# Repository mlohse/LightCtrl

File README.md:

# LightCtrl

Light Controller for Egret TenV4 electric scooter

The goal of this project is to power the scooter's front light from the main LiPo battery instead of using 4x throw-away alkaline batteries (AAA).
Further, it allows the light to be switched on/off conveniently via the throttle controller's power button (same as the rear light)
or have the light switched on/off automatically when it's getting dark (e.g. in tunnels or at night).

The PCB needs to be installed into the front light's battery compartment. The on/off switch is no longer needed and can be replaced by a photo transistor.

A short demo video (German) is available on vimeo: https://vimeo.com/364582430

# Required Skills
Before you consider building your own, please be aware that you'll need some skills here:

* You should be able to solder SMD! I've chosen large components (1206) for the PCB, but of course there is the 44-pin package of the ATMEGA, which may need some practice and a decent solder iron/station.

* The PCB and front light is powered via the 5V USB supply of the scooters throttle controller and needs to be connected in series to the throttle controller's tx data line (white cable).
  This can be accomplished by either opening/modifying the throttle controller (see instructions below) or creating an adapter cable which can be installed between the throttle and the motor controller (in the battery compartment).

* The front light's plastic case needs some mechanical modification to fit a cable through the housing (drill a hole) and fit PCB into the battery compartment.

* You'll need to remove the front light's on/off switch and solder wire between the voltage regulators enable pin (again SMD) and ground, see description below...

* You'll need an ISP-programmer for flashing the firmware (those are available on Ebay for ~15 Euro)

This project is certainly not suitable for beginners and of course I won't take any liability if you break your scooter or any components of it.

# Bill of Material (BOM)
The PCB can be ordered at OSH Park (they ship worldwide):

* https://oshpark.com/shared_projects/gwnaN0r6 (rev.B)

It doesn't really matter of which brand/type you order resistors and capacitors, nor does this board require any tight tolerances. You can purchase whatever your local hardware dealer has on stock fitting the value/package described by the schematic.
However, for convenience I've created a virtual shopping basket at Reichelt Elektronik:

* https://www.reichelt.de/my/1627216

Unfortunately, the AQY212EH isn't available at Reichelt, but you can order it from Buerklin,
Order-No.: 29G8736

* https://www.buerklin.com/de/Produkte/Elektromechanik/Relais-und-Sch%C3%BCtze/PhotoMOS-Relais/AQY-212-EHA%2C-SMD-Relais/p/29G8736

Further, I've tried several (low-cost) usb cables from Amazon which didn't quite fit my needs, until I came across these 2:

* https://www.amazon.de/gp/product/B01I1HXRK8/ (this is actually much shorter than 40cm, I measured only 34cm!)

* https://www.amazon.de/gp/product/B00P0ES0VC/

The UGreen USB3 extension cable is of decent quality and can be crimped perfectly into the Micromatch connector.
(Yes, it needs to be cut into halves: The female connector is needed for the front light, the male can be used to build an adapter for the ISP programmer)

# Building and Flashing the Firmware
You need to have an AVR toolchain installed (make, gcc, binutils)

On Arch Linux simply install the following packages:

`# pacman -S community/avr-gcc community/avr-binutils community/avr-libc`

I'm still using my good old AVR Dragon (unfortunately, it seems to be out of production), which needs to have avrdude installed:

`# pacman -S avrdude`

If you own a different programmer there is a good chance it's also supported by avrdude, otherwise just install whatever software it needs and don't forget to adopt the programmer/fuses section of the Makefile accordingly.

To build the firmware change into the `src` directory and run:

`# make`

...then connect the board to your ISP programmer (it needs to be powered through the programmer!) and flash the fuses:

`# make fuses`

...and firmware:

`# make program`

Done.

# Front Light PCB Modification
1. Remove the on/off switch and undervoltage indicator led (no longer needed)
2. Connect the voltage regulator's enable pin (outer pin) to GND, as shown:

# Throttle Controller Modification
1. Open the throttle controller (it is glued with silicone and requieres some force - use a knife or sharp piece of metal). Once open remove the USB socket which is also glued in with silicone and clean it as best as you can:

2. Unsolder the TX data wire (white, labels as T6):

3. Open the solder bridge between the USB data lines:

4. Conntect the white cabel (which was soldered to throttle T6 previously) to the USB data line and add a new cable from the other usb data line to the throttle's T6 pin. Note: the 4k7 resistor is optional. If it is installed the scooter can be started without the LightCtrl pcb connected. If it is not fitted, the throttle will show an error if powered on without it. This may be usefull as a weak theft-protection (if you take the front-light with you when you leave the scooter alone).

5. Use some hot glue to put the USB socket back in
Important: After modification the USB socket can no longer be used to charge usb devices! Do not plug in your cell phone!

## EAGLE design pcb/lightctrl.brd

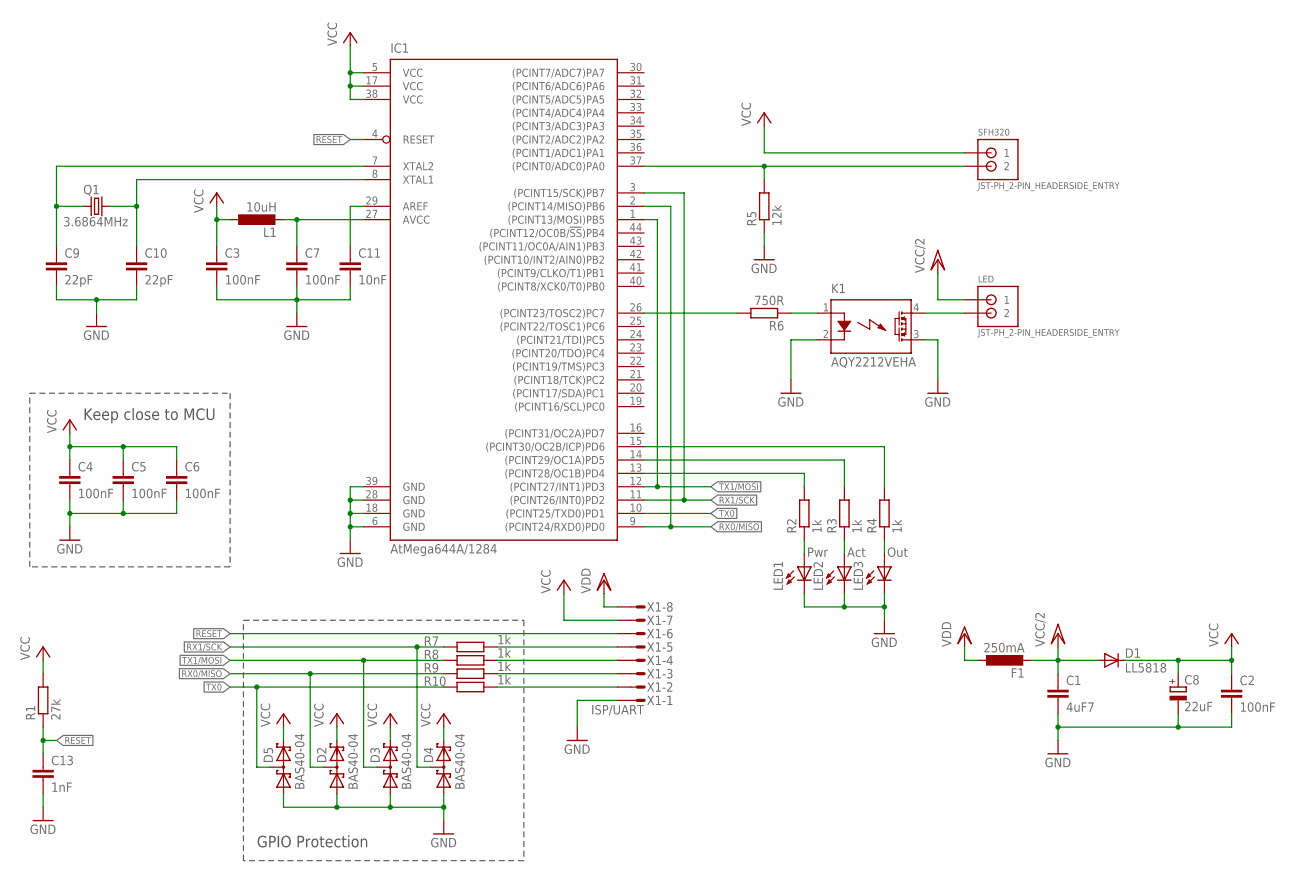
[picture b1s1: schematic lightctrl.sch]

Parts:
C1: 4uF7; C1206
C2, C3, C4, C5, C6, C7: 100nF; C1206
C8: 22uF; SMC_D
C9, C10: 22pF; C1206
C11: 10nF; C1206
C13: 1nF; C1206
D1: LL5818; MELF-MLL41
D2, D3, D4, D5: BAS40-04; SOT23
F1: 250mA; L1812
IC1: AtMega644A/1284; TQFP44
K1: AQY2212VEHA; SMD-DIP04
L1: 10uH; L3230M
LED: JST-PH_2-PIN_HEADERSIDE_ENTRY; S2B-PH_HEADER
LED1: Pwr; CHIPLED_1206
LED2: Act; CHIPLED_1206
LED3: Out; CHIPLED_1206
Q1: 3.6864MHz; HC49UP
R1: 27k; R1206
R2, R3, R4, R7, R8, R9, R10: 1k; R1206
R5: 12k; R1206
R6: 750R; R1206
SFH320: JST-PH_2-PIN_HEADERSIDE_ENTRY; S2B-PH_HEADER
X1: ISP/UART; MICROMATCH-8

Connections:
GND: C1.2, C2.2, C3.2, C4.2, C5.2, C6.2, C7.2, C8.-, C9.2, C10.2, C11.2, C13.2, D2.1 (A1), D3.1 (A1), D4.1 (A1), D5.1 (A1), IC1.6 (GND), IC1.18 (GND), IC1.28 (GND), IC1.39 (GND), K1.2 (K), K1.3 (DS2), LED1.C, LED2.C, LED3.C, R5.1, X1.1
unnamed: C7.1, IC1.27 (AVCC), L1.2
unnamed: IC1.37 ((PCINT0/ADC0)PA0), R5.2, SFH320.P2 (2)
unnamed: C11.1, IC1.29 (AREF)
unnamed: C10.1, IC1.8 (XTAL1), Q1.2
unnamed: C9.1, IC1.7 (XTAL2), Q1.1
unnamed: K1.4 (DS1), LED.P2 (2)
unnamed: LED1.A, R2.1
unnamed: LED2.A, R3.1
unnamed: LED3.A, R4.1
unnamed: IC1.13 ((PCINT28/OC1B)PD4), R2.2
unnamed: IC1.14 ((PCINT29/OC1A)PD5), R3.2
unnamed: IC1.15 ((PCINT30/OC2B/ICP)PD6), R4.2
unnamed: R7.2, X1.5
unnamed: K1.1 (A), R6.1
unnamed: R8.2, X1.4
unnamed: R9.2, X1.3
unnamed: IC1.26 ((PCINT23/TOSC2)PC7), R6.2
unnamed: R10.2, X1.2
RESET: C13.1, IC1.4 (RESET), R1.1, X1.6
RX0/MISO: D2.3 (C1A2), IC1.2 ((PCINT14/MISO)PB6), IC1.9 ((PCINT24/RXD0)PD0), R9.1
RX1/SCK: D4.3 (C1A2), IC1.3 ((PCINT15/SCK)PB7), IC1.11 ((PCINT26/INT0)PD2), R7.1
TX0: D5.3 (C1A2), IC1.10 ((PCINT25/TXD0)PD1), R10.1
TX1/MOSI: D3.3 (C1A2), IC1.1 ((PCINT13/MOSI)PB5), IC1.12 ((PCINT27/INT1)PD3), R8.1
VCC: C2.1, C3.1, C4.1, C5.1, C6.1, C8.+, D1.C, D2.2 (C2), D3.2 (C2), D4.2 (C2), D5.2 (C2), IC1.5 (VCC), IC1.17 (VCC), IC1.38 (VCC), L1.1, R1.2, SFH320.P1 (1), X1.7
VCC/2: C1.1, D1.A, F1.2, LED.P1 (1)
VDD: F1.1, X1.8

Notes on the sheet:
GPIO Protection
Keep close to MCU

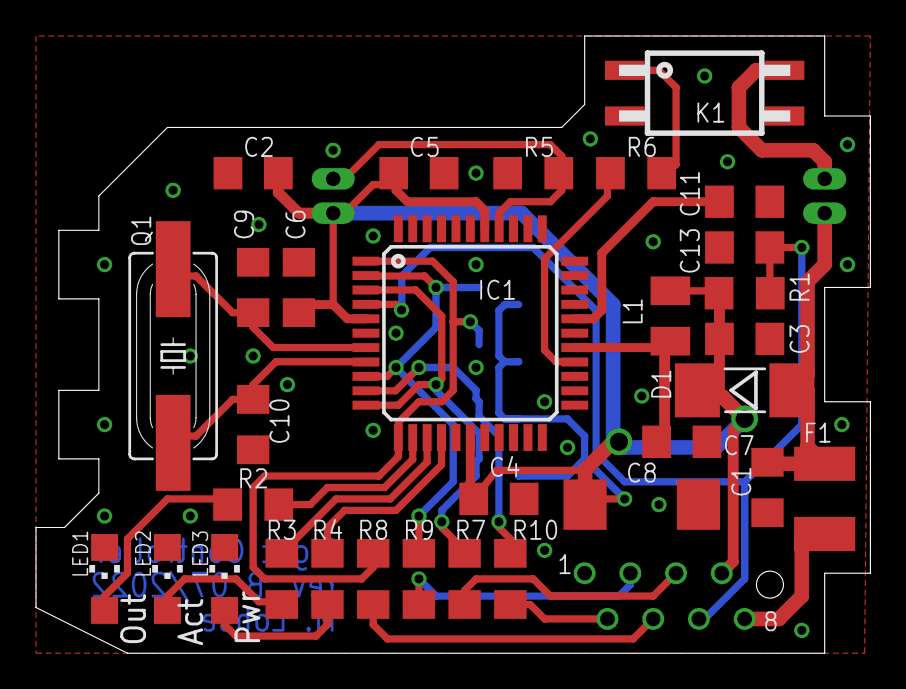
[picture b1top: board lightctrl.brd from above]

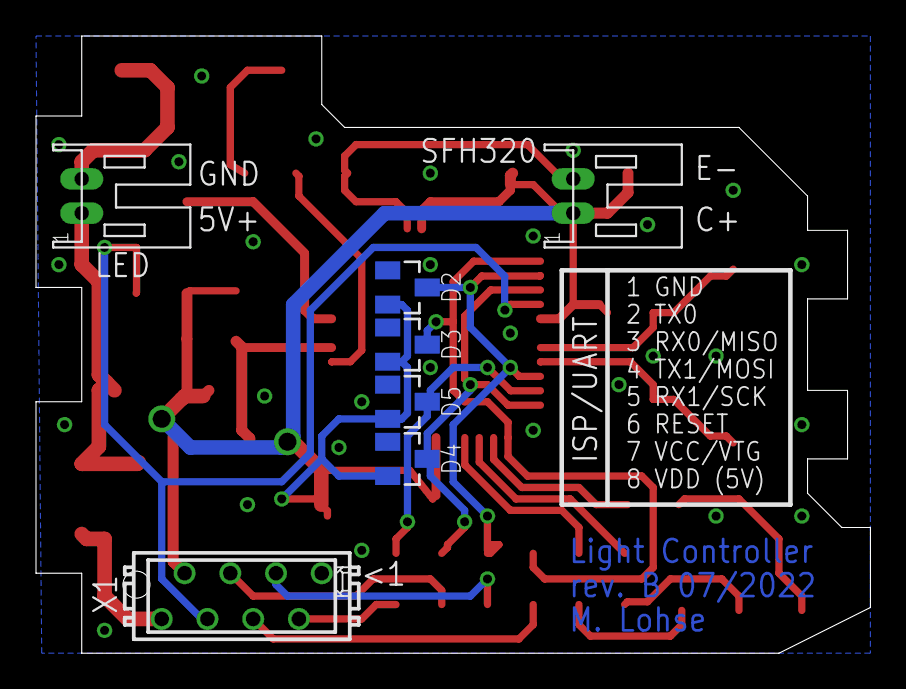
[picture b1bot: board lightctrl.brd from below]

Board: 2 copper layers, 46.4 x 34.3 mm, 38 parts (7 on the bottom side), 27 nets.

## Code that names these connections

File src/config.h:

/*******************************************************************************
 * Config file for Egret Light Controller board rev. A                         *
 * author:  Markus Lohse <mlohse@gmx.net>                                      *
 * date:    2019-09-24                                                         *
 * license: LGPLv3, see https://www.gnu.org/licenses/lgpl-3.0.txt              *
 ******************************************************************************/
#ifndef CONFIG_H_
#define CONFIG_H_

/***********************************
 * IO Ports                        *
 ***********************************/
#define IO_DDRA                 0xFE    // PortA [1..7] unused out, 0 sensor input
#define IO_DDRB                 0x1F    // PortB [0..4] unused out, 5 mosi/tx1 -> PD3 in, 6 miso/rx0 -> PD0 in, 7 sck/rx1 -> PD2 in
#define IO_DDRC                 0xFF    // PortC [0..6] unused out 7 switch out
#define IO_DDRD                 0x8C    // PortD [0,1] UART0 in, [2,3] UART1 unused out, [4..6] LED1-3 out, 7 unused out

/* led definition for led.h */
#define PORT_LED0               PORTC
#define PORT_LED1               PORTD
#define PORT_LED2               PORTD
#define PORT_LED3               PORTD
#define PIN_LED0                7       // light switch, simply treat it as led
#define PIN_LED1                4       // Pwr - blue
#define PIN_LED2                5       // Act - green
#define PIN_LED3                6       // Out - red

#define LED_NUM                 4

/* to be used with led_on, led_off,... */
#define LED_LIGHT               0
#define LED_PWR                 1
#define LED_ACT                 2
#define LED_OUT                 3


/***********************************
 * Initialization                  *
 ***********************************/
#define INIT_PORTA              0x00    // pull unused pins to GND, disable pullup on PortA,0 (light sensor)
#define INIT_PORTB              0x00    // pull unused pins to GND, disable pullups for mosi/miso/sck
#define INIT_PORTC              0x00    // pull unused pins to GND, switch off led light
#define INIT_PORTD              0x00    // pull unused pins to GND, switch off leds, disable pullup on UART(s)


/***********************************
 * UART Settings                   *
 ***********************************/
#define BUFFER_SIZE_TX0         32      // in bytes, must be between 1 and 255, should be at least (UART_MSG_SIZE_MAX * 2) + 2
#define BUFFER_SIZE_TX1         1
#define BUFFER_SIZE_RX0         32
#define BUFFER_SIZE_RX1         36
#define UART0_ENABLE                    // undefine to disable uart interface(s)
//#define UART1_ENABLE

/* baud rate */
#define UART0_UBRR              0x005F  // @3.6864MHz -> 2400Baud
#define UART1_UBRR              0x0077


/***********************************
 * Throttle/Display Controller     *
 ***********************************/
#define THROTTLE_VERSION        0       // V4 = 0 or V3X = 1 (see msg.h)


/***********************************
 * Light sensor                    *
 ***********************************/
#define LIGHT_SENS_PORT         PORTA
#define LIGHT_SENS_PIN          0       // PortA,0
#define LIGHT_SENS_THRES_OFF    150     // ADC threshold for switching light off
#define LIGHT_SEND_THRES_ON     60      // ADC threshold for switching light on
//#define LIGHT_AUTO_INTERVAL_MAX 10000   // autolight toggle max. interval in msec


/***********************************
 * Sleep Mode                      *
 ***********************************/
#define SLEEP_BOD_DISABLE               // uncomment to disable brown out detect during sleep (reduces pwr consumption)
#define SLEEP_WAKEUP_PCINT      14      // wakeup on pin change irq PB6 (rx0/mosi)
#define SLEEP_ACT_TIMEOUT       1750    // fall asleep after not receiving any uart message for x milliseconds

#endif /* CONFIG_H_ */

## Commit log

2019-10-03 initial version
2019-10-03 add project description and BOM
2019-10-03 add section for firmware building and flashing
2019-10-06 add video url
2019-10-06 make init() static
2020-12-13 update project description and add cover image
2020-12-13 compatibility update: scooter firmware ver. 9.3
2020-12-14 add instructions for modifying throttle controller and front light's pcb
2023-01-29 Add Avr ISP programmer to Makefile
2023-01-29 Fix typos
2023-01-29 Update pcb and documentation to rev.B: fix padsize for D1, add gpio protection for MCU, slightly widen board to get better grip in battery compartment
